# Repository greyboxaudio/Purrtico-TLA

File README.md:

Based on the AMEK TLA (Transformer Like Amplifier) balanced Input & Output circuits.

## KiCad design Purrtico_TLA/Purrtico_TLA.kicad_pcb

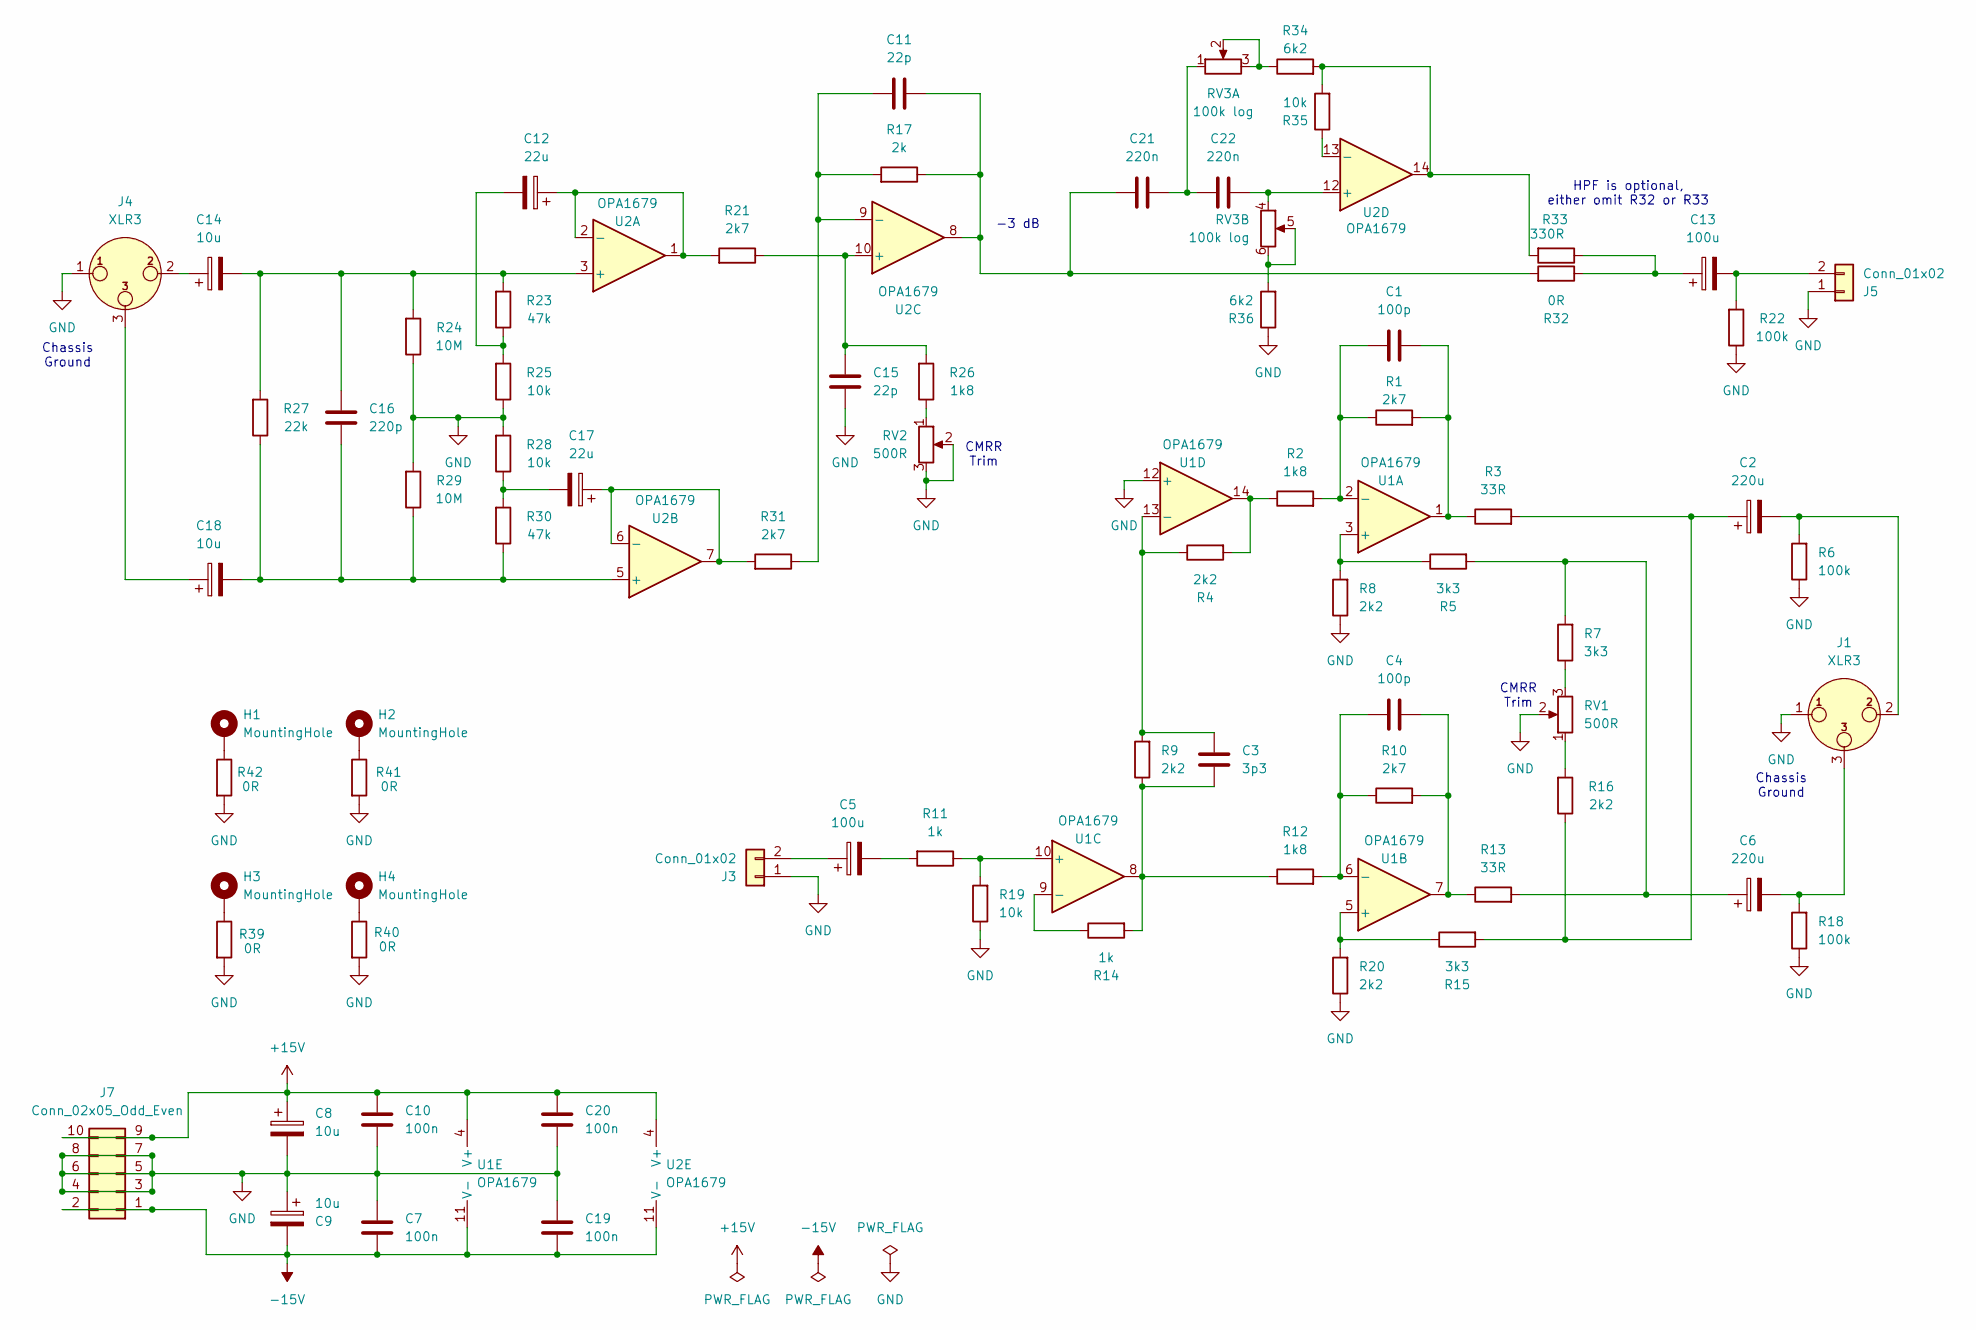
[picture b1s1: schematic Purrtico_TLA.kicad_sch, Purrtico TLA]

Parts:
C1, C4: 100p; C_1206_3216Metric
C2, C6: 220u; CP_Radial_D8.0mm_P3.50mm
C3: 3p3; C_1206_3216Metric
C5, C13: 100u; CP_Radial_D6.3mm_P2.50mm
C7, C10, C19, C20: 100n; C_1206_3216Metric
C8, C9, C14, C18: 10u; CP_Radial_D6.3mm_P2.50mm
C11, C15: 22p; C_1206_3216Metric
C12, C17: 22u; CP_Radial_D6.3mm_P2.50mm
C16: 220p; C_1206_3216Metric
C21, C22: 220n; C_Rect_L7.2mm_W2.5mm_P5.00mm_FKS2_FKP2_MKS2_MKP2
H1, H2, H3, H4: MountingHole; MountingHole_3.2mm_M3_DIN965_Pad
J1, J4: XLR3; PinHeader_1x03_P2.54mm_Vertical
J3, J5: Conn_01x02; PinHeader_1x02_P2.54mm_Vertical
J7: Conn_02x05_Odd_Even; PinHeader_2x05_P2.54mm_Vertical
R1, R10, R21, R31: 2k7; R_1206_3216Metric
R2, R12, R26: 1k8; R_1206_3216Metric
R3, R13: 33R; R_1206_3216Metric
R4, R8, R9, R16, R20: 2k2; R_1206_3216Metric
R5, R7, R15: 3k3; R_1206_3216Metric
R6, R18, R22: 100k; R_1206_3216Metric
R11, R14: 1k; R_1206_3216Metric
R17: 2k; R_1206_3216Metric
R19, R25, R28, R35: 10k; R_1206_3216Metric
R23, R30: 47k; R_1206_3216Metric
R24, R29: 10M; R_1206_3216Metric
R27: 22k; R_1206_3216Metric
R32, R39, R40, R41, R42: 0R; R_1206_3216Metric
R33: 330R; R_1206_3216Metric
R34, R36: 6k2; R_1206_3216Metric
RV1, RV2: 500R; PinHeader_1x03_P2.54mm_Vertical
RV3: 100k log; PinHeader_2x03_P2.54mm_Vertical
U1, U2: OPA1679; SOIC-14_3.9x8.7mm_P1.27mm

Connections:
+15V: C8.1, C10.2, C20.2, J7.9, J7.10, U1.4 (V+), U2.4 (V+)
-15V: C7.1, C9.2, C19.1, J7.1, J7.2, U1.11 (V-), U2.11 (V-)
GND: C7.2, C8.2, C9.1, C10.1, C15.2, C19.2, C20.1, J1.1, J3.1, J4.1, J5.1, J7.3, J7.4, J7.5, J7.6, J7.7, J7.8, R6.1, R8.1, R18.1, R19.1, R20.1, R22.1, R24.1, R25.1, R28.2, R29.2, R36.1, R39.2, R40.2, R41.2, R42.2, RV1.2, RV2.2, RV2.3, U1.12 (+)
unnamed: C1.2, R1.2, R3.1, U1.1
unnamed: C2.1, R3.2, R15.2, R16.1
unnamed: C2.2, J1.2, R6.2
unnamed: C3.1, R9.1, R12.1, R14.2, U1.8
unnamed: C4.2, R10.2, R13.1, U1.7
unnamed: C5.2, R11.2
unnamed: C6.1, R5.2, R7.2, R13.2
unnamed: C6.2, J1.3, R18.2
unnamed: C11.1, C21.1, R17.1, R32.2, U2.8
unnamed: C12.2, R23.1, R25.2
unnamed: C13.1, R32.1, R33.1
unnamed: C14.1, J4.2
unnamed: C17.2, R28.1, R30.2
unnamed: C18.1, J4.3
unnamed: C21.2, C22.1, RV3.1
unnamed: H1.1, R42.1
unnamed: H2.1, R41.1
unnamed: H3.1, R39.1
unnamed: H4.1, R40.1
unnamed: C5.1, J3.2
unnamed: C13.2, J5.2, R22.2
unnamed: R2.1, R4.2, U1.14
unnamed: R7.1, RV1.3
unnamed: R16.2, RV1.1
unnamed: R26.1, RV2.1
unnamed: R33.2, R34.2, R35.2, U2.14
unnamed: R34.1, RV3.2, RV3.3
unnamed: R36.2, RV3.5, RV3.6
unnamed: R5.1, R8.2, U1.3 (+)
unnamed: C1.1, R1.1, R2.2, U1.2 (-)
unnamed: R15.1, R20.2, U1.5 (+)
unnamed: C4.1, R10.1, R12.2, U1.6 (-)
unnamed: R11.1, R19.2, U1.10 (+)
unnamed: R14.1, U1.9 (-)
unnamed: C3.2, R4.1, R9.2, U1.13 (-)
unnamed: C14.2, C16.2, R23.2, R24.2, R27.2, U2.3 (+)
unnamed: C12.1, R21.2, U2.1, U2.2 (-)
unnamed: C16.1, C18.2, R27.1, R29.1, R30.1, U2.5 (+)
unnamed: C17.1, R31.2, U2.6 (-), U2.7
unnamed: C15.1, R21.1, R26.2, U2.10 (+)
unnamed: C11.2, R17.2, R31.1, U2.9 (-)
unnamed: C22.2, RV3.4, U2.12 (+)
unnamed: R35.1, U2.13 (-)

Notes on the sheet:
HPF is optional, either omit R32 or R33
CMRR Trim
Chassis Ground
-3 dB

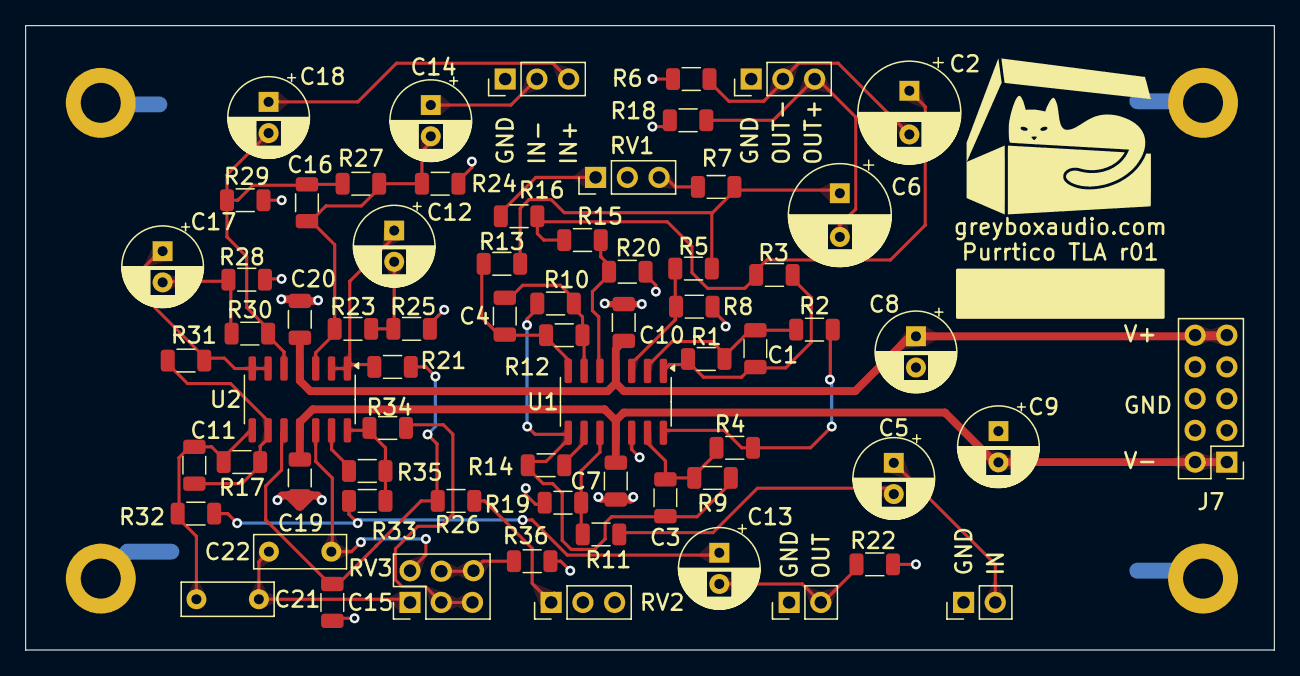
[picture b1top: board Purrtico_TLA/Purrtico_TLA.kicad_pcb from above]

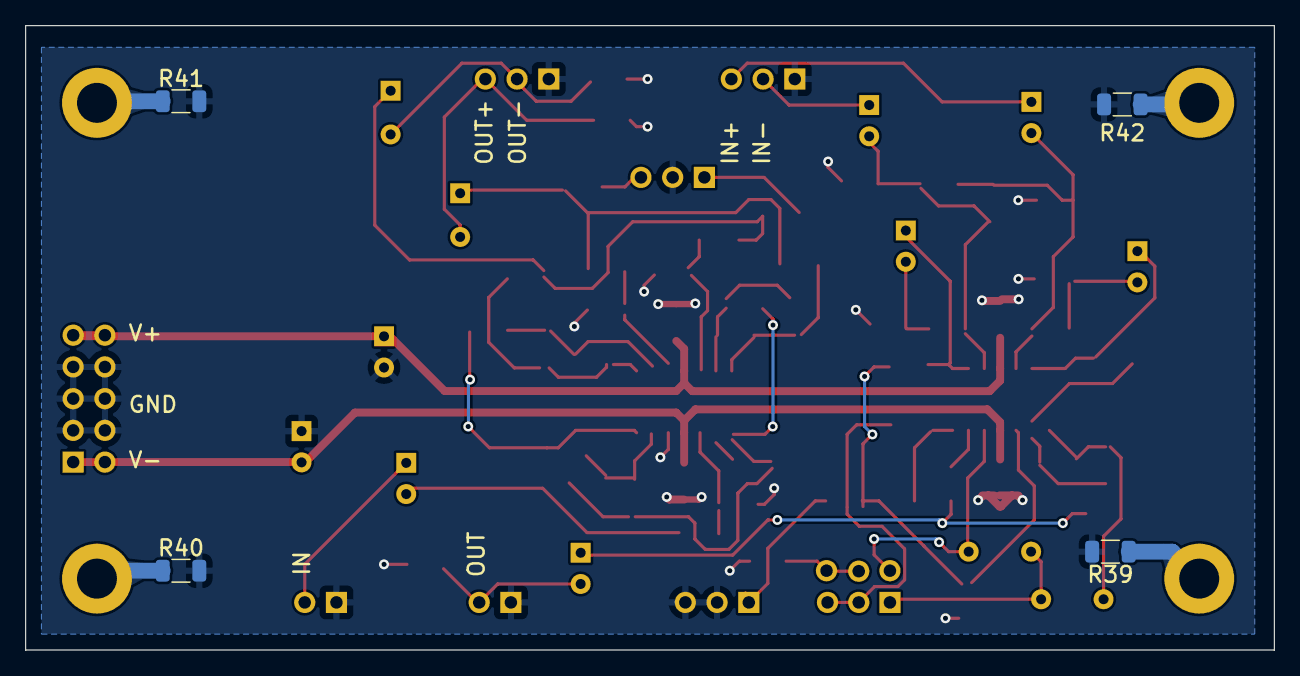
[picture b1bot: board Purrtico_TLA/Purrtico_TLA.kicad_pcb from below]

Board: 2 copper layers, 100.0 x 50.0 mm, 76 parts (4 on the bottom side), 46 nets.

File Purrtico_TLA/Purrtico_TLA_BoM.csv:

"Reference","Value","Qty","Datasheet","Footprint","DNP"
"C1,C4","100p","2","~","Capacitor_SMD:C_1206_3216Metric",""
"C2,C6","220u","2","~","Capacitor_THT:CP_Radial_D8.0mm_P3.50mm",""
"C3","3p3","1","~","Capacitor_SMD:C_1206_3216Metric",""
"C5,C13","100u","2","~","Capacitor_THT:CP_Radial_D6.3mm_P2.50mm",""
"C7,C10,C19,C20","100n","4","~","Capacitor_SMD:C_1206_3216Metric",""
"C8,C9,C14,C18","10u","4","~","Capacitor_THT:CP_Radial_D6.3mm_P2.50mm",""
"C11,C15","22p","2","~","Capacitor_SMD:C_1206_3216Metric",""
"C12,C17","22u","2","~","Capacitor_THT:CP_Radial_D6.3mm_P2.50mm",""
"C16","220p","1","~","Capacitor_SMD:C_1206_3216Metric",""
"C21,C22","220n","2","~","Capacitor_THT:C_Rect_L7.2mm_W2.5mm_P5.00mm_FKS2_FKP2_MKS2_MKP2",""
"J1,J4","XLR3","2","~","Connector_PinHeader_2.54mm:PinHeader_1x03_P2.54mm_Vertical",""
"J3,J5","Conn_01x02","2","~","Connector_PinHeader_2.54mm:PinHeader_1x02_P2.54mm_Vertical",""
"J7","Conn_02x05_Odd_Even","1","~","Connector_PinHeader_2.54mm:PinHeader_2x05_P2.54mm_Vertical",""
"R1,R10,R21,R31","2k7","4","~","Resistor_SMD:R_1206_3216Metric",""
"R2,R12,R26","1k8","3","~","Resistor_SMD:R_1206_3216Metric",""
"R3,R13","33R","2","~","Resistor_SMD:R_1206_3216Metric",""
"R4,R8,R9,R16,R20","2k2","5","~","Resistor_SMD:R_1206_3216Metric",""
"R5,R7,R15","3k3","3","~","Resistor_SMD:R_1206_3216Metric",""
"R6,R18,R22","100k","3","~","Resistor_SMD:R_1206_3216Metric",""
"R11,R14","1k","2","~","Resistor_SMD:R_1206_3216Metric",""
"R17","2k","1","~","Resistor_SMD:R_1206_3216Metric",""
"R19,R25,R28,R35","10k","4","~","Resistor_SMD:R_1206_3216Metric",""
"R23,R30","47k","2","~","Resistor_SMD:R_1206_3216Metric",""
"R24,R29","10M","2","~","Resistor_SMD:R_1206_3216Metric",""
"R27","22k","1","~","Resistor_SMD:R_1206_3216Metric",""
"R32,R39,R40,R41,R42","0R","5","~","Resistor_SMD:R_1206_3216Metric",""
"R33","330R","1","~","Resistor_SMD:R_1206_3216Metric",""
"R34,R36","6k2","2","~","Resistor_SMD:R_1206_3216Metric",""
"RV1,RV2","500R","2","~","Connector_PinHeader_2.54mm:PinHeader_1x03_P2.54mm_Vertical",""
"RV3","100k log","1","~","Connector_PinHeader_2.54mm:PinHeader_2x03_P2.54mm_Vertical",""
"U1,U2","OPA1679","2","http://www.ti.com/lit/ds/symlink/opa1678.pdf","Package_SO:SOIC-14_3.9x8.7mm_P1.27mm",""

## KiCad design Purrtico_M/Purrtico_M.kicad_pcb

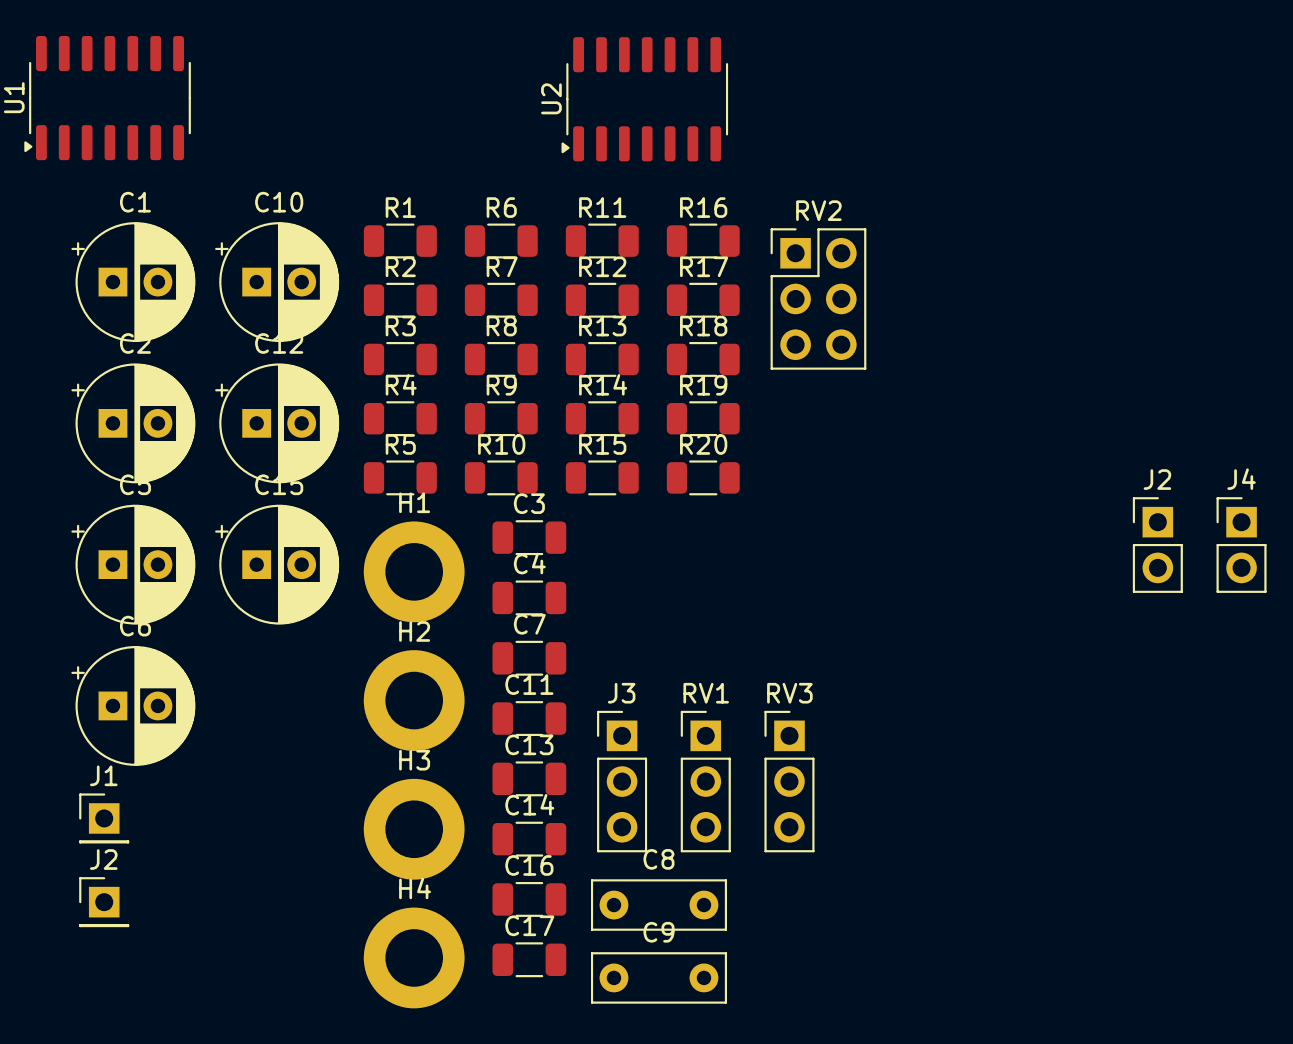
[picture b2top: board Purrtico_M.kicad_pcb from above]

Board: 2 copper layers, 51 parts (0 on the bottom side), 32 nets, no tracks yet.

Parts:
C1, C2, C5, C6, C10: 100u; CP_Radial_D6.3mm_P2.50mm
C3, C4, C7, C11: 100p; C_1206_3216Metric
C8, C9: 5n6; C_Rect_L7.2mm_W2.5mm_P5.00mm_FKS2_FKP2_MKS2_MKP2
C12, C15: 10u; CP_Radial_D6.3mm_P2.50mm
C13, C14, C16, C17: 100n; C_1206_3216Metric
H1, H2, H3, H4: MountingHole; MountingHole_3.2mm_M3_DIN965_Pad
J1, J2: Conn_01x01_Pin; PinHeader_1x01_P2.54mm_Vertical
J2#2, J4: Conn_01x02; PinHeader_1x02_P2.54mm_Vertical
J3: Conn_01x03; PinHeader_1x03_P2.54mm_Vertical
R1, R2, R3, R4, R6, R7: 2k7; R_1206_3216Metric
R5: 1k; R_1206_3216Metric
R8, R18: 1k8; R_1206_3216Metric
R9, R11: 270R; R_1206_3216Metric
R10, R13: 1k5; R_1206_3216Metric
R12, R15: 390R; R_1206_3216Metric
R14: 330R; R_1206_3216Metric
R16: 1k2; R_1206_3216Metric
R17: 47k; R_1206_3216Metric
R19: 22k; R_1206_3216Metric
R20: 8k2; R_1206_3216Metric
RV1: 4k7; PinHeader_1x03_P2.54mm_Vertical
RV2: 10k; PinHeader_2x03_P2.54mm_Vertical
RV3: 10k; PinHeader_1x03_P2.54mm_Vertical
U1, U2: OPA1679; SOIC-14_3.9x8.7mm_P1.27mm

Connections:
+15V: C12.1, C13.1, C14.1, J3.3, U1.4 (V+), U2.4 (V+)
-15V: C15.2, C16.2, C17.2, J3.2, U1.11 (V-), U2.11 (V-)
GND: C12.2, C13.2, C14.2, C15.1, C16.1, C17.1, H1.1, H2.1, H3.1, H4.1, J2#2.1, J3.1, J4.1, R5.1, R12.1, R15.1, U1.3 (+), U1.10 (+), U1.12 (+), U2.3 (+), U2.5 (+), U2.10 (+), U2.12 (+)
unnamed: C1.1, C3.2, R1.2, R4.1, U1.1
unnamed: C1.2, RV1.1
unnamed: C2.1, C4.2, C6.1, R2.2, U1.7
unnamed: C2.2, RV1.3
unnamed: C5.2, R3.1
unnamed: C7.2, R7.2, R9.2, U2.1
unnamed: C8.2, R11.1, R18.2, R19.1, U2.7
unnamed: C9.2, R6.2, U2.8
unnamed: C10.1, RV3.2
unnamed: C10.2, R16.2
unnamed: C11.1, R14.1, R16.1, R17.1, R20.2, RV3.3, U2.14
unnamed: C5.1, J2#2.2
unnamed: C6.2, J4.2
unnamed: R8.1, RV1.2
unnamed: R9.1, RV2.1
unnamed: R10.1, RV2.2
unnamed: R11.2, RV2.4
unnamed: R12.2, RV2.3
unnamed: R13.2, RV2.5
unnamed: R15.2, RV2.6
unnamed: C3.1, R1.1, R3.2, U1.2 (-)
unnamed: R5.2, R14.2, U1.5 (+)
unnamed: C4.1, R2.1, R4.2, R19.2, U1.6 (-)
unnamed: U1.8, U1.9 (-)
unnamed: U1.13 (-), U1.14
unnamed: C7.1, R6.1, R7.1, R8.2, R20.1, U2.2 (-)
unnamed: C8.1, R10.2, U2.6 (-)
unnamed: C9.1, R13.1, U2.9 (-)
unnamed: C11.2, R17.2, R18.1, RV3.1, U2.13 (-)

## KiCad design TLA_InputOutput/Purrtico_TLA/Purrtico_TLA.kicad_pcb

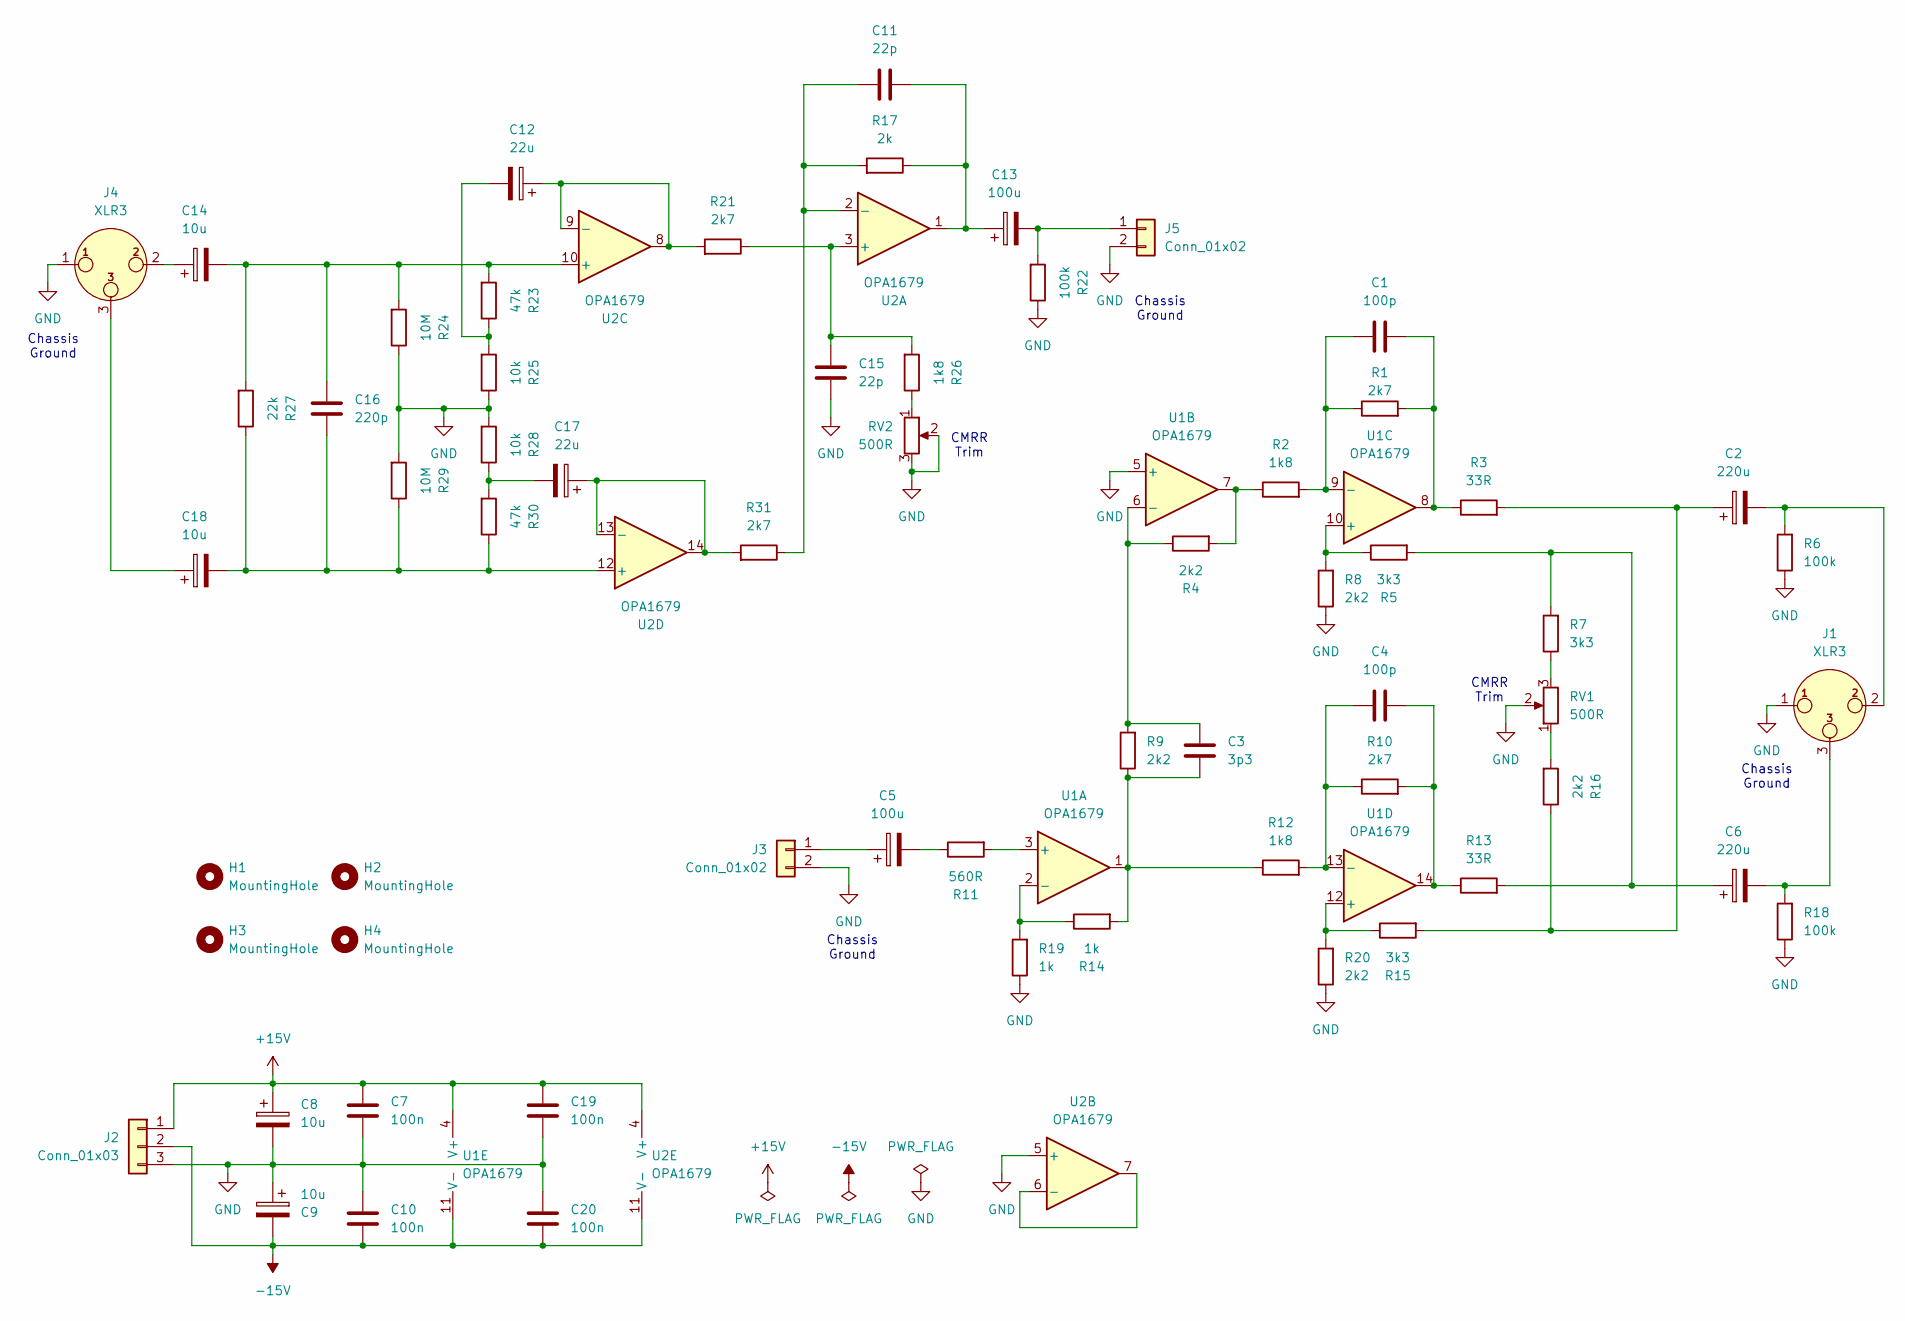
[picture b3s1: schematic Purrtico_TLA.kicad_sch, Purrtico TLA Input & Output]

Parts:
C1, C4: 100p; C_1206_3216Metric
C2, C6: 220u; CP_Radial_D8.0mm_P3.50mm
C3: 3p3; C_1206_3216Metric
C5, C13: 100u; CP_Radial_D6.3mm_P2.50mm
C7, C10, C19, C20: 100n; C_1206_3216Metric
C8, C9, C14, C18: 10u; CP_Radial_D6.3mm_P2.50mm
C11, C15: 22p; C_1206_3216Metric
C12, C17: 22u; CP_Radial_D6.3mm_P2.50mm
C16: 220p; C_1206_3216Metric
H1, H2, H3, H4: MountingHole; MountingHole_3.2mm_M3_DIN965
J1, J4: XLR3; PinHeader_1x03_P2.54mm_Vertical
J2: Conn_01x03; PinHeader_1x03_P2.54mm_Vertical
J3, J5: Conn_01x02; PinHeader_1x02_P2.54mm_Vertical
R1, R10, R21, R31: 2k7; R_1206_3216Metric
R2, R12, R26: 1k8; R_1206_3216Metric
R3, R13: 33R; R_1206_3216Metric
R4, R8, R9, R16, R20: 2k2; R_1206_3216Metric
R5, R7, R15: 3k3; R_1206_3216Metric
R6, R18, R22: 100k; R_1206_3216Metric
R11: 560R; R_1206_3216Metric
R14, R19: 1k; R_1206_3216Metric
R17: 2k; R_1206_3216Metric
R23, R30: 47k; R_1206_3216Metric
R24, R29: 10M; R_1206_3216Metric
R25, R28: 10k; R_1206_3216Metric
R27: 22k; R_1206_3216Metric
RV1, RV2: 500R; PinHeader_1x03_P2.54mm_Vertical
U1, U2: OPA1679; SOIC-14_3.9x8.7mm_P1.27mm

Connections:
+15V: C7.1, C8.1, C19.1, J2.1, U1.4 (V+), U2.4 (V+)
-15V: C9.2, C10.2, C20.2, J2.2, U1.11 (V-), U2.11 (V-)
GND: C7.2, C8.2, C9.1, C10.1, C15.2, C19.2, C20.1, J1.1, J2.3, J3.2, J4.1, J5.2, R6.1, R8.1, R18.1, R19.1, R20.1, R22.1, R24.1, R25.1, R28.2, R29.2, RV1.2, RV2.2, RV2.3, U1.5 (+), U2.5 (+)
unnamed: C1.2, R1.2, R3.1, U1.8
unnamed: C2.1, R3.2, R15.2, R16.1
unnamed: C2.2, J1.2, R6.2
unnamed: C3.1, R9.1, R12.1, R14.2, U1.1
unnamed: C4.2, R10.2, R13.1, U1.14
unnamed: C5.2, R11.1
unnamed: C6.1, R5.2, R7.2, R13.2
unnamed: C6.2, J1.3, R18.2
unnamed: C11.1, C13.1, R17.1, U2.1
unnamed: C12.2, R23.1, R25.2
unnamed: C14.1, J4.2
unnamed: C17.2, R28.1, R30.2
unnamed: C18.1, J4.3
unnamed: C5.1, J3.1
unnamed: C13.2, J5.1, R22.2
unnamed: R2.1, R4.2, U1.7
unnamed: R7.1, RV1.3
unnamed: R16.2, RV1.1
unnamed: R26.1, RV2.1
unnamed: R11.2, U1.3 (+)
unnamed: R14.1, R19.2, U1.2 (-)
unnamed: C3.2, R4.1, R9.2, U1.6 (-)
unnamed: R5.1, R8.2, U1.10 (+)
unnamed: C1.1, R1.1, R2.2, U1.9 (-)
unnamed: R15.1, R20.2, U1.12 (+)
unnamed: C4.1, R10.1, R12.2, U1.13 (-)
unnamed: C15.1, R21.1, R26.2, U2.3 (+)
unnamed: C11.2, R17.2, R31.1, U2.2 (-)
unnamed: U2.6 (-), U2.7
unnamed: C14.2, C16.2, R23.2, R24.2, R27.2, U2.10 (+)
unnamed: C12.1, R21.2, U2.8, U2.9 (-)
unnamed: C16.1, C18.2, R27.1, R29.1, R30.1, U2.12 (+)
unnamed: C17.1, R31.2, U2.13 (-), U2.14

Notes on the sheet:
Chassis Ground
CMRR Trim

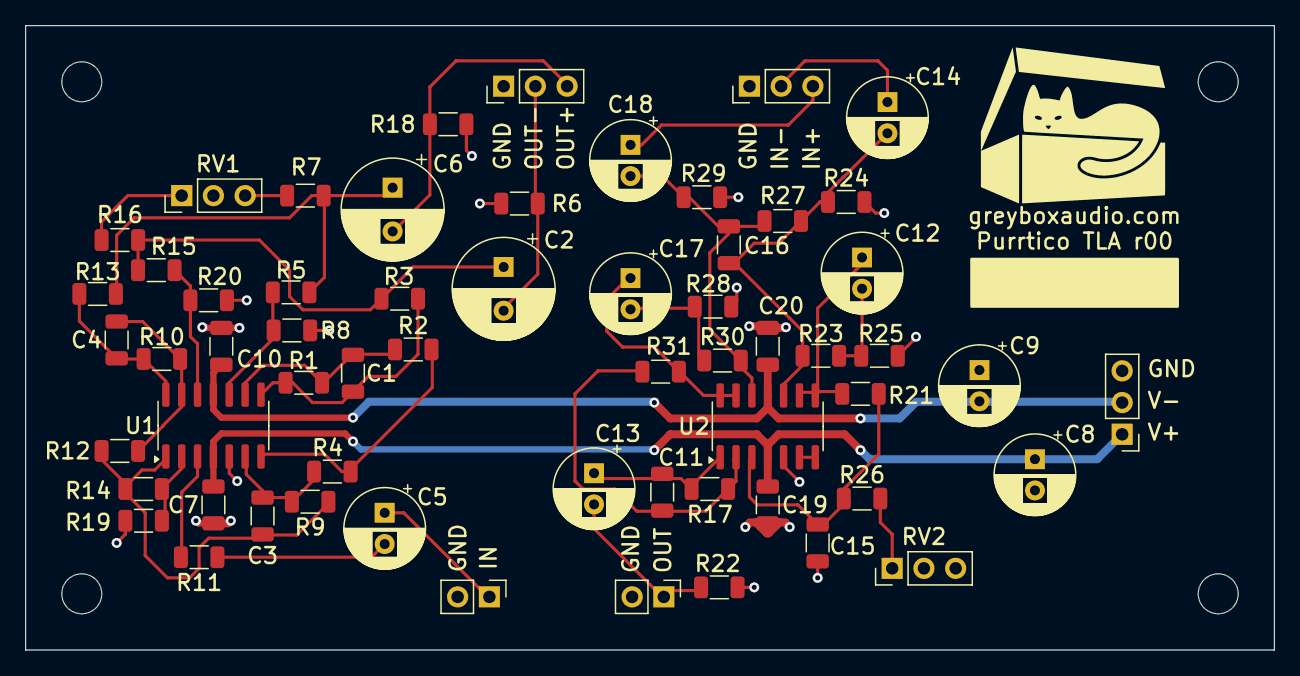
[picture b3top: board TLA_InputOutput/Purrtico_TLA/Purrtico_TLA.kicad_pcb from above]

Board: 2 copper layers, 100.0 x 50.0 mm, 64 parts (0 on the bottom side), 36 nets.

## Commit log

2024-05-06 update layout
2024-05-07 massive pcb rework
2024-05-07 pcb update
2024-05-08 pcb cleanup
2024-05-08 update pcb
2024-05-09 added TLA Input
2024-05-09 added comments
2024-05-09 updated comment layout
2024-05-09 update traces
2024-05-09 added more vias
2024-05-09 PCB now has an Uterus
2024-05-10 renamed to Purrtico
2024-05-12 added logo as symbol
2024-05-12 re-oriented resistors
2024-05-13 update pcb layout
2024-05-14 added mounting holes
2024-05-14 added jlcpcb settings
2024-05-23 update PCB to r01
2024-05-23 move folder
2024-05-23 remove folders
2024-05-25 2k2 & mounting
    made R7 & R16 equal value, added copper mounting holes
2024-05-25 cleaned up tracks
2024-05-25 input trim & teardrops
    replaced 560R resistor with a 10k trim pot, added teardrops to THT- & IC-Pads
2024-05-30 added 0R resistors
    added 0R resistors to make the unused opamp potentially usable
2024-07-18 started purrtico m eq
    singla band only, for testing
2024-07-18 moved files
2024-07-18 update 0R resistors
2024-07-20 update pcb
    swapped position of input/output, replaced power connector with a 10pin eurorack connector
2024-08-04 update circuit
2024-08-04 update annotation
    parity with final r00
2024-08-04 Create Purrtico-TLA_BoM
2024-08-04 update BoM
2024-08-15 added optional HPF
2024-08-15 added bottom labels
2024-08-15 switch HPF knob
2024-08-16 added fabrication outputs
2024-08-16 moved rv3
